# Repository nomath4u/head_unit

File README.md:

# Custom Bluetooth Headunit

## Summary

The idea behind this project is to get a lightweight bluetooth stereo
into any car. The amount of exposed unit will be customizable (If you want a
screen on it you will want to be able to see it). But should be able to function
with only the microphone showing, allowing the rest of the DIN area to be used 
for other things

##Included in this repository

As I work on this project I will be adding additional thing. For now there is
only the INO file in order to program the microcontroller that will be used 
with the unit. As well as a tool to help send commands to the rn-52. Eventually there will be a wiring diagram for prototyping with
a parts list and then an eagle schematic and parts list so the board can be
ordered and then put together and reflowed. After that, separate STL files for 
parts that will need to be 3d printed will be added based on common
configurations.

## Bugs in V1.0
CMD enable is wired to GPIO10 instead of 9
USBD- is not wired at all
Power input is not exposed

## Bugs in V1.1
Still yet to be discovered

## Proposed Configurations

## Schematic

### Minimal

In the minimal configuration only the microphone will be exposed. The board 
will be mounted on the back of any 3d printed part with only a hole for the
microphone and no buttons will be broken out. In this configuration everything
will need to be controlled from the phone

### Standard

In this configuration we have the same setup as the Minimal except with buttons
broken out for play/pause, next/previous track, and a few other buttons.

### Large

In this configuration a screen is involved. On this creen the Title, artist,
and album name of the song will displayed as well as a customizable background.
This is implemented with a SPI TFT screen. There are many different sizes
available from adafruit so as requests are made different STL files and code
defines will have to be made in order to accomodate the different screens

##NOTE

* You will want an amplifier for this to be in normal volume range. There is a 
preamplifier on the bluetooth part but without an amplifier you won't be able
to hear it when at highway speeds. As of V1.1 There are spaces for 2 LM386s which help. It may be loud enough on its own for you if you use those connections.

## Useful setup tips
Update to version 1.16 first. Many settings don't work as expected without doing that
Use the added uart_via_arduino code in order to relay commands through an arduino
to the RN-52. Make sure your arduino is @ 3.3V.

Commands I liked
S%,86 // Enableds reconnect on power-on, discoverable on startup, and disables system tones
SN,<name_here> //Name your device.
SS,0F //Turn up the internal amplifier to the max (may want to use something different depending on your amp

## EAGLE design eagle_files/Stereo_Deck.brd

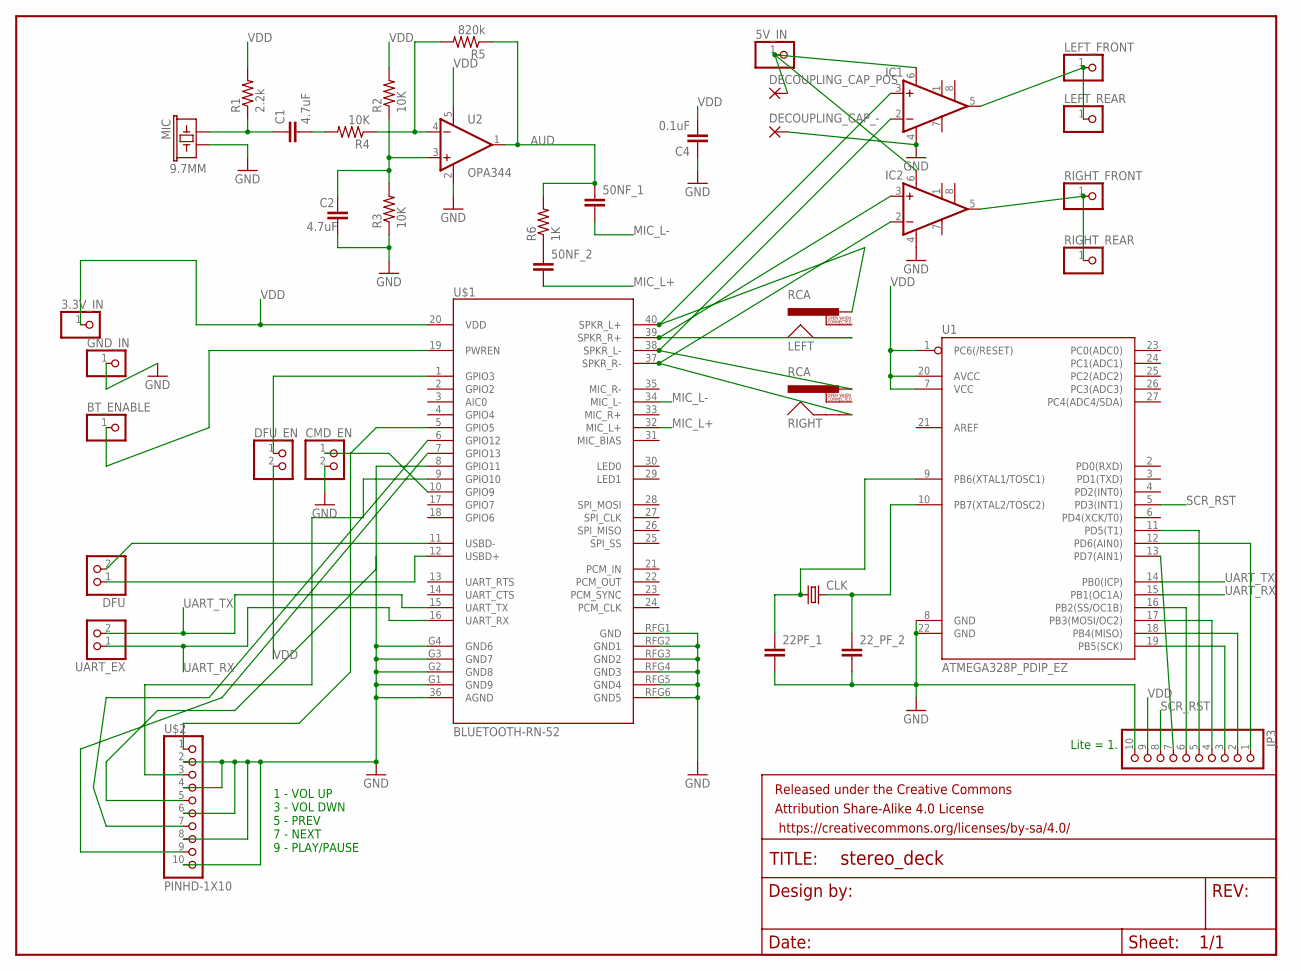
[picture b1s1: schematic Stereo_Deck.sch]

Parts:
3.3V_IN, 5V_IN: PINHD-1X1; 1X01
22PF_1, 22_PF_2, 50NF_1, 50NF_2: CC0603; C0603
BT_ENABLE: PINHD-1X1; 1X01
C1, C2: 4.7uF; 0603-CAP
C4: 0.1uF; 0603-CAP
CLK: CRYSTALHC49US; HC49US
CMD_EN: PINHD-1X2; 1X02
DECOUPLING_CAP_-: 2,15/1,0
DECOUPLING_CAP_POS: 2,15/1,0
DFU: PINHD-1X2; 1X02
DFU_EN: PINHD-1X2; 1X02
FRAME1: FRAME-LETTER; CREATIVE_COMMONS
GND_IN: PINHD-1X1; 1X01
IC1, IC2: LM386N-1; DIL08
JP3: PINHD-1X10; 1X10
LEFT: RCA
LEFT_FRONT: PINHD-1X1; 1X01
LEFT_REAR: PINHD-1X1; 1X01
MIC: 9.7MM; MIC-9.7MM
R1: 2.2k; 0603-RES
R2, R3, R4: 10K; 0603-RES
R5: 820k; 0603-RES
R6: 1K; 0603-RES
RIGHT: RCA
RIGHT_FRONT: PINHD-1X1; 1X01
RIGHT_REAR: PINHD-1X1; 1X01
U1: ATMEGA328P_PDIP_EZ; DIL28-EZ
U2: OPA344; SOT23-5
U$1: BLUETOOTH-RN-52; RN-52
U$2: PINHD-1X10; 1X10-BIG
UART_EX: PINHD-1X2; 1X02

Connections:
AUD: 50NF_1.1, R5.1, R6.2, U2.1 (OUT)
CMD_EN: CMD_EN.1, U$1.10 (GPIO9)
DFU_EN: DFU_EN.1, U$1.1 (GPIO3)
GND: 22PF_1.2, 22_PF_2.2, C2.2, C4.1, CMD_EN.2, DECOUPLING_CAP_-.1, GND_IN.1, IC1.4 (GND), IC2.4 (GND), JP3.10, MIC.2, R3.1, U1.8 (GND), U1.22 (GND), U2.2 (V-), U$1.36 (AGND), U$1.G1 (GND9), U$1.G2 (GND8), U$1.G3 (GND7), U$1.G4 (GND6), U$1.RFG1 (GND), U$1.RFG2 (GND1), U$1.RFG3 (GND2), U$1.RFG4 (GND3), U$1.RFG5 (GND4), U$1.RFG6 (GND5), U$2.2, U$2.4, U$2.6, U$2.8, U$2.10
MIC_L+: 50NF_2.2, U$1.32 (MIC_L+)
MIC_L-: 50NF_1.2, U$1.34 (MIC_L-)
unnamed: 22PF_1.1, CLK.1, U1.9 (PB6(XTAL1/TOSC1))
unnamed: JP3.1, U1.12 (PD6(AIN0))
unnamed: JP3.2, U1.18 (PB4(MISO))
unnamed: IC1.3 (+IN), LEFT.PIN, U$1.40 (SPKR_L+)
unnamed: IC2.3 (+IN), LEFT.SHELL, U$1.39 (SPKR_R+)
unnamed: IC1.2 (-IN), RIGHT.PIN, U$1.38 (SPKR_L-)
unnamed: DFU.2, U$1.11 (USBD-)
unnamed: DFU.1, U$1.12 (USBD+)
unnamed: BT_ENABLE.1, U$1.19 (PWREN)
unnamed: JP3.3, U1.19 (PB5(SCK))
unnamed: JP3.4, U1.17 (PB3(MOSI/OC2))
unnamed: JP3.5, U1.11 (PD5(T1))
unnamed: JP3.6, U1.16 (PB2(SS/OC1B))
unnamed: JP3.7, U1.13 (PD7(AIN1))
unnamed: 22_PF_2.1, CLK.2, U1.10 (PB7(XTAL2/TOSC2))
unnamed: C1.1, MIC.1, R1.1
unnamed: IC2.2 (-IN), RIGHT.SHELL, U$1.37 (SPKR_R-)
unnamed: R4.1, R5.2, U2.4 (-IN)
unnamed: C1.2, R4.2
unnamed: C2.1, R2.1, R3.2, U2.3 (+IN)
unnamed: 50NF_2.1, R6.1
unnamed: 5V_IN.1, DECOUPLING_CAP_POS.1, IC1.6 (VS), IC2.6 (VS)
unnamed: U$1.5 (GPIO5), U$2.1
unnamed: U$1.9 (GPIO10), U$2.3
unnamed: U$1.8 (GPIO11), U$2.5
unnamed: U$1.6 (GPIO12), U$2.7
unnamed: U$1.7 (GPIO13), U$2.9
unnamed: IC2.5 (OUT), RIGHT_FRONT.1, RIGHT_REAR.1
unnamed: IC1.5 (OUT), LEFT_FRONT.1, LEFT_REAR.1
SCR_RST: JP3.8, U1.5 (PD3(INT1))
UART_RX: U1.15 (PB1(OC1A)), U$1.16 (UART_RX), UART_EX.1
UART_TX: U1.14 (PB0(ICP)), U$1.15 (UART_TX), UART_EX.2
VDD: 3.3V_IN.1, C4.2, JP3.9, R1.2, R2.2, U1.1 (PC6(/RESET)), U1.7 (VCC), U1.20 (AVCC), U2.5 (V+), U$1.20 (VDD)

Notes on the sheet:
Lite = 1.
1 - VOL UP 3 - VOL DWN 5 - PREV 7 - NEXT 9 - PLAY/PAUSE

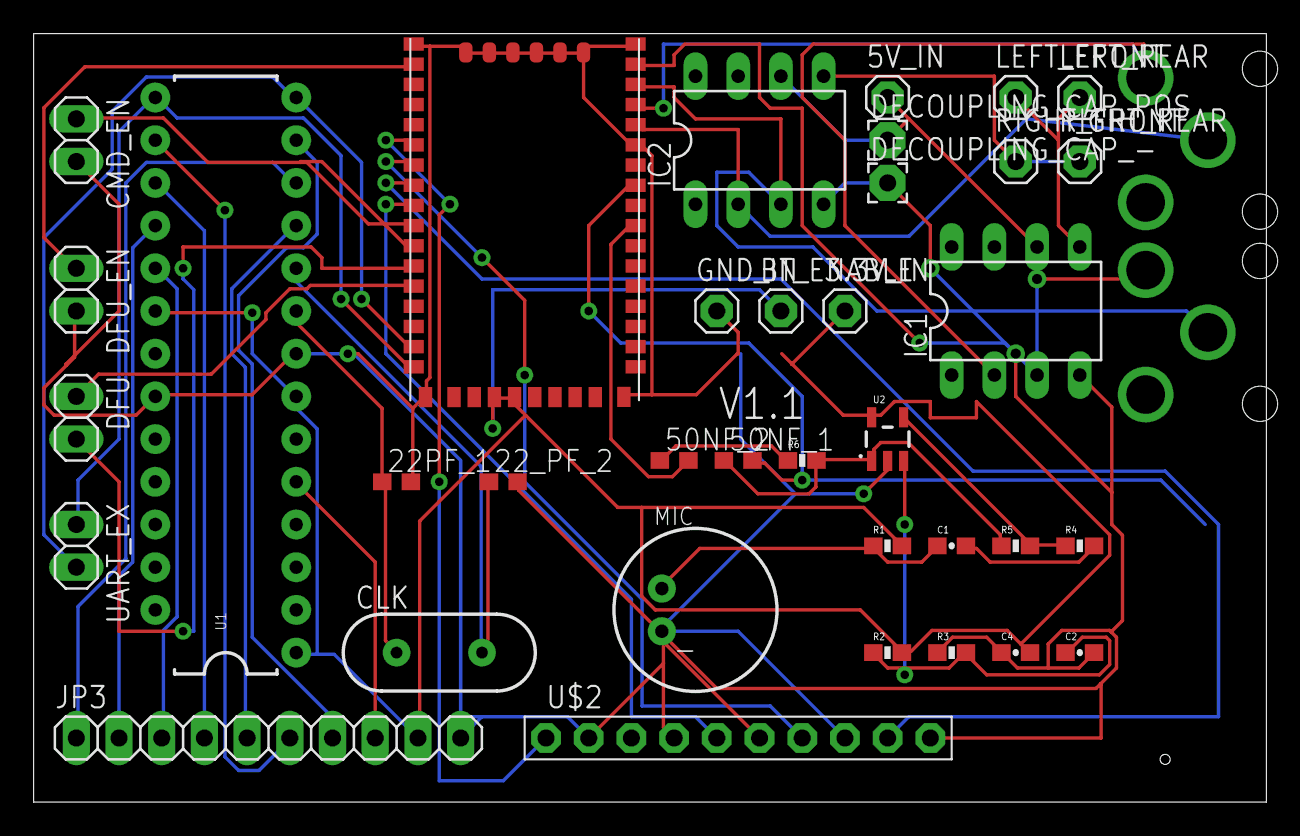
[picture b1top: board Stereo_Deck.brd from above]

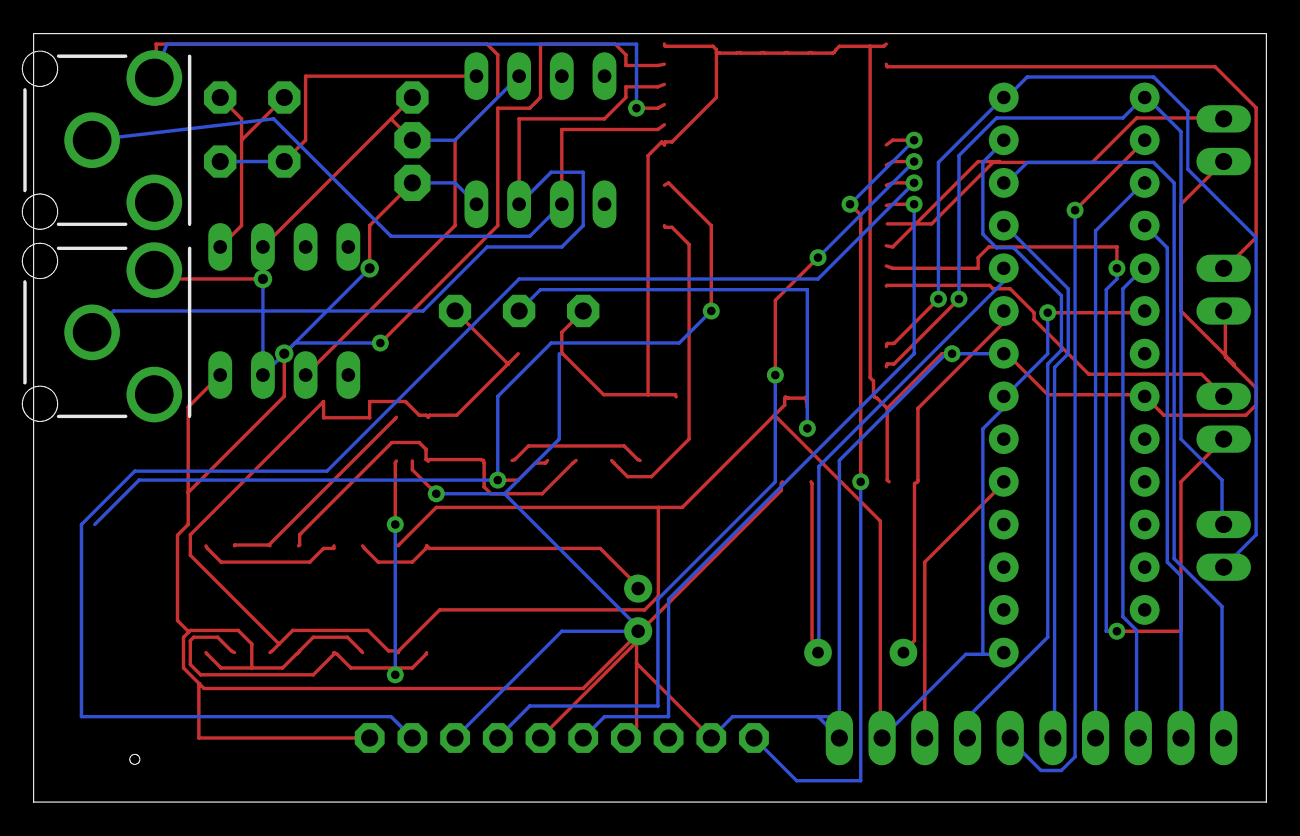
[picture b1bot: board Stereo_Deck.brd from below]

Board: 2 copper layers, 73.3 x 45.7 mm, 39 parts (2 on the bottom side), 39 nets.

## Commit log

2016-09-21 first commit. Screen is displaying metadata
2016-09-21 Updated README with more information
2016-09-21 Cleaned up old commented out code that won't be used anymore. Also added ideas for speed improvements
2016-09-21 Added initialization of SD card as well as drawing the background image. (Untested)
2016-09-21 Added drawing functions for each piece of info wanting to be drawn on the screen from the metadata
2016-09-21 Added parsing for fields from the metadata message and calling of the draw and parse functions to place the text on the screen. (Untested)
2016-09-22 Now actually working. Also rewrote metadata gathering function
2018-06-03 Updated with more information now that I have tired the external communications exposures
2019-06-13 Added hopefully only necessary eagle files to reproduce?
2019-06-13 Updated silkscreen for new board version
2019-06-13 Add picture of the schematic (hopefully
2019-06-13 Previous picture add didn't work
2019-06-13 Hopefully image working

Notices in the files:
parts and their libraries:
SparkFun-Aesthetics: Licensing: Creative Commons ShareAlike 4.0 International - https://creativecommons.org/licenses/by-sa/4.0
SparkFun-Aesthetics: Released under the Creative Commons Attribution Share-Alike 4.0 License
SparkFun-Aesthetics: https://creativecommons.org/licenses/by-sa/4.0
